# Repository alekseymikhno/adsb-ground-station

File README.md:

# ADS-B 1090 MHz Ground Station (PDX Airspace)

A 1090 MHz ADS-B receiver system tracking aircraft over Portland, OR, paired with an in-progress custom RF front end and an LLM-based anomaly-detection pipeline.

## Status

- **Pi 5 receiver**: Live and collecting flight data (May–July 2026)
- **Custom RF front end**: In design: 1090 MHz filter-LNA (TA1090EC SAW + PGA-103+). Schematic and QucsStudio simulation complete (~13.3 dB cascade gain, ~3.2 dB NF); not yet sent to fabrication.
- **Anomaly detection**: LLM analysis pipeline in development

## What It Does

1. **RF capture**: 1090 MHz antenna -> TA1090EC SAW filter -> PGA-103+ LNA -> Nooelec NESDR SMArt v5 SDR
2. **Decode**: Raspberry Pi 5 runs dump1090 to decode Mode S / ADS-B messages in real time
3. **Analysis**: LLM-based anomaly detector flags unusual flight patterns over PDX airspace
4. **Output**: Logged to SQLite, served via web dashboard with a Tar1090 UI

## Folder Structure

- `hardware/rf-frontend/` — KiCad schematic, PCB layout, component libraries
  - `kicad/` — schematic and board files
  - `simulation/` — QucsStudio S-parameter simulations and results
- `software/receiver/` — dump1090 config, startup scripts
- `software/anomaly-detection/` — analysis pipeline code
- `docs/` — datasheets, system diagrams, build photos
- `data/rf-measurements/` — NanoVNA measurement data (S-parameter sweeps)

## Key Specs

**RF Front End: 1090 MHz Filter-LNA (TA1090EC + PGA-103+)**

| Parameter | Value | Source |
|-----------|-------|--------|
| Cascade gain @ 1.09 GHz | ~13.3 dB | Friis analysis (sim + datasheet) |
| System noise figure | ~3.2 dB | Friis cascade |
| LNA gain (S21) @ 1.09 GHz | ~15.6 dB | QucsStudio simulation |
| LNA noise figure | ~0.9 dB | PGA-103+ datasheet |
| Input match (S11) @ 1.09 GHz | −13.7 dB | QucsStudio simulation |
| Front filter | TA1090EC SAW, ~2.3 dB insertion loss | TAI-SAW datasheet |
| Topology | SAW filter → PGA-103+ E-pHEMT LNA, bias-tee | — |
| Port impedance | 50 Ω in/out (no external matching) | — |
| Supply | 4.5 V via bias-tee choke | — |

*Simulated/calculated values pending hardware validation. NanoVNA measurement data in `/data/rf-measurements/`.*

**Receiver**

- Nooelec NESDR SMArt v5 SDR with software-activatable bias tee
- dump1090 decode on Raspberry Pi 5
- Coverage: PDX airspace (~130-140 nm radius)

## Design Notes

The front end places a SAW filter ahead of the LNA (filter-first topology). This trades a small noise-figure penalty, the filter's ~2.3 dB insertion loss adds directly to system NF per the Friis equation, for out-of-band rejection of FM broadcast, cellular, and GSM signals that would otherwise overload the SDR in a high-RF environment near an airport. The PGA-103+ was chosen for its sub-1 dB noise figure and 50 Ω matched ports requiring no external matching network.

## Roadmap

1. Finalize schematic and PCB layout; export Gerbers
2. Fabricate and assemble the filter-LNA board
3. NanoVNA validation against simulated gain / match
4. Integrate measured front-end performance into system characterization
5. Complete anomaly-detection pipeline and dashboard

## References

- [Mode S / ADS-B protocol (mode-s.org)](https://mode-s.org/)
- [dump1090 (flightaware fork)](https://github.com/flightaware/dump1090)
- [RTL-SDR Blog V4](https://www.rtl-sdr.com/rtl-sdr-blog-v4-release/)
- [PGA-103+ datasheet (Mini-Circuits)](https://www.minicircuits.com/pdfs/PGA-103+.pdf)

## License

MIT

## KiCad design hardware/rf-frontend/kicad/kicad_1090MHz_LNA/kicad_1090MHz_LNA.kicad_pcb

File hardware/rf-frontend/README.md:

# RF Front End

KiCad schematic and PCB design for the 1090 MHz ADS-B filter-LNA-filter chain.
- Target NF: ~2.85 dB
- Target gain: +32 dB
- Status: Design phase, pending PCB fabrication

See `/docs/friis-cascade-analysis.pdf` for the full cascade analysis.

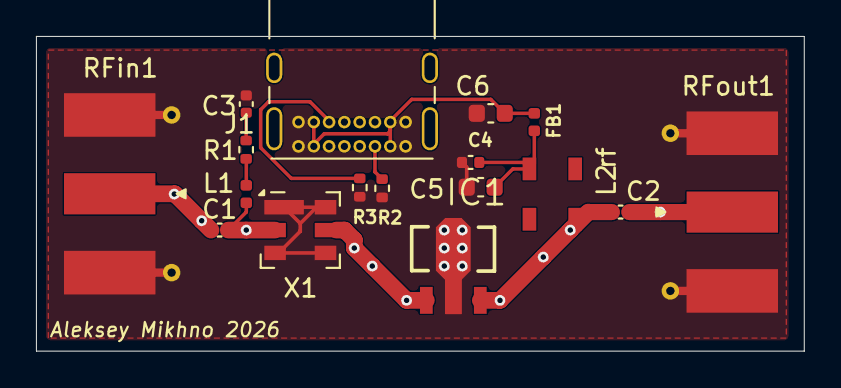
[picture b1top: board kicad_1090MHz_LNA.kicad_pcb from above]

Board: 2 copper layers, 42.7 x 17.5 mm, 17 parts (0 on the bottom side), 12 nets.

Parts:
C1, C2, C3, C4: C; C_0402_1005Metric
C5, C6: C; C_0603_1608Metric
FB1: FerriteBead; L_0402_1005Metric
IC1: PGA-103_; SOT-89
J1: USB_C_Receptacle_USB2.0_16P; USB_C_Receptacle_GCT_USB4085
L1: L; L_0402_1005Metric
L2: TCCH-80; GU1604
R1, R2, R3: R; R_0402_1005Metric
RFin1: 732511150; SMA_Molex_73251-1153_EdgeMount_Horizontal
RFout1: 732511150; SMA_Molex_73251-1153_EdgeMount_Horizontal
X1: STA1090EC; Filter_SAW-6_3.8x3.8mm

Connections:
GND: C3.1, C4.2, C5.2, C6.2, IC1.2 (GND), J1.A1 (GND), J1.A12 (GND), J1.B1 (GND), J1.B12 (GND), R2.1, R3.1, RFin1.2, RFout1.2, X1.1 (GND), X1.3 (GND), X1.4 (GND), X1.6 (GND)
unnamed: C1.1, RFin1.1
unnamed: C2.2, RFout1.1
unnamed: C3.2, R1.2
unnamed: C6.1, FB1.1, J1.A4 (VBUS), J1.A9 (VBUS), J1.B4 (VBUS), J1.B9 (VBUS)
unnamed: IC1.1 (IN), X1.5 (OUT)
unnamed: C2.1, IC1.3 (OUT/DC), L2.P$1 (RF)
unnamed: J1.A5 (CC1), R2.2
unnamed: J1.B5 (CC2), R3.2
unnamed: L1.2, R1.1
unnamed: C4.1, C5.1, FB1.2, L2.P$3 (DC)
unnamed: C1.2, L1.1, X1.2 (IN)

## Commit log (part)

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2026-06-30 Create 1090MHz Bias-T LNA (PGA-103+)
